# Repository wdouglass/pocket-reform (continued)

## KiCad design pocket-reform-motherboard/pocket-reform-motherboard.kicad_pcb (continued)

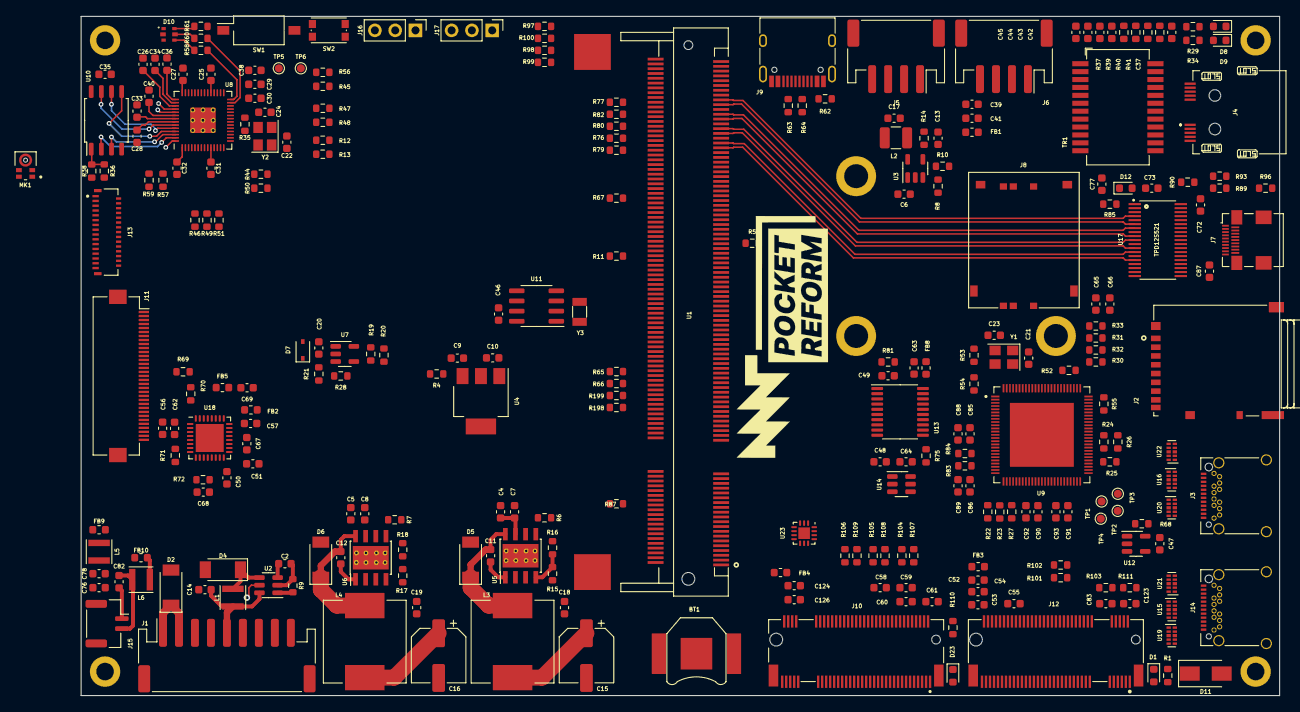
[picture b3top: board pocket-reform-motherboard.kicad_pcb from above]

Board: 6 copper layers, 150.0 x 85.0 mm, 274 parts (0 on the bottom side), 284 nets.

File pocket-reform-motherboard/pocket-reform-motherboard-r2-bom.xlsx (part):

Reference | Value | Footprint | Manufacturer | Manufacturer_No | Qty
C1, C3, C13, C20, C25, C27-C33, C35, C38, C40, C42-C50, C53-C55, C57, C59-C64, 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 | 0.1uF | Capacitor_SMD:C_0402_1005Metric | Samsung | CL05B104KO5NNNC | 66
C2, C4, C5, C39, C51, C56, C65, C98, C105, C107 | 10uF | Capacitor_SMD:C_0603_1608Metric | Samsung | CL10A106MO8NQNC | 10
C6, C17 | 22uF | Capacitor_SMD:C_0603_1608Metric | Samsung | CL10A226MP8NUNE | 2
C7, C8, C11, C12, C18, C19, C52, C58 | 10nF | Capacitor_SMD:C_0603_1608Metric | Samsung | CL10B103KB8NNNC | 8
C9, C10, C26, C34, C36, C41 | 1uF | Capacitor_SMD:C_0603_1608Metric | Samsung | CL10A105KB8NNNC | 6
C14, C83, C123, C124, C126 | 47uF | Capacitor_SMD:C_0603_1608Metric | Murata | GRM188R60J476ME15D | 5
C15, C16 | 330uF | Capacitor_SMD:CP_Elec_6.3x5.4 | Lelon | VZT331M0JTR-0606ACS | 2
C21, C23 | 18pF | Capacitor_SMD:C_0603_1608Metric | Yageo | CC0603JRNPO9BN180 | 2
C22, C24 | 27pF | Capacitor_SMD:C_0603_1608Metric | Yageo | CC0603JRNPO9BN270 | 2
C37 | 1nF | Capacitor_SMD:C_0603_1608Metric | Yageo | CC0603KRX7R9BB102 | 1
C67, C106 | 22uF | Capacitor_SMD:C_0805_2012Metric | Samsung | CL10A226MP8NUNE | 2
C82 | 470nF | Capacitor_SMD:C_0603_1608Metric | Samsung | CL10B474KA8NNNC | 1
C94, C100 | 10uF | Capacitor_SMD:C_0402_1005Metric | Samsung | CL05A106MP5NUNC | 2
C96 | DNP | Capacitor_SMD:C_0402_1005Metric | Samsung | CL05B104KO5NNNC | 1
C102, C103 | 47uF | Capacitor_SMD:C_1206_3216Metric | Murata | GRM31CR61A476ME15L | 2
D1 | LED_MODEM | LED_SMD:LED_0603_1608Metric | Everlight | 19-217/R6C-AL1M2VY/3T | 1
D2, D4-D6 | PMEG4050EP,115 | Diode_SMD:D_SOD-128 | Nexperia | PMEG4050EP,115 | 4
D3 | PMEG1020EA,115 | Diode_SMD:D_SOD-323 | Nexperia | PMEG1020EA,115 | 1
D8, D9 | LED_Small | LED_SMD:LED_0603_1608Metric | Everlight | 19-217/R6C-AL1M2VY/3T | 2
D10 | 19-337/R6GHBHC-A01/2T | footprints:LED_19-337_R6GHBHC-A01_2T | Everlight | 19-337/R6GHBHC-A01/2T | 1
D11 | SS54 | Diode_SMD:D_SMA | MDD | SS54 | 1
D12 | SD0603S040S0R2 | Diode_SMD:D_0603_1608Metric | AVX | SD0603S040S0R2 | 1
D23 | LED_NVME | LED_SMD:LED_0603_1608Metric | Everlight | 19-217/R6C-AL1M2VY/3T | 1
FB1, FB7, FB11 | 220@100MHz 1.4A | Inductor_SMD:L_0603_1608Metric | Murata | BLM18KG221SN1D | 3
FB2-FB4, FB6, FB8-FB10, FB12-FB16 | 100@100MHz 3A | Inductor_SMD:L_0603_1608Metric | Murata | BLM18PG121SN1D | 12
FB5 | DNP | Inductor_SMD:L_0603_1608Metric | Murata | BLM18PG121SN1D | 1
H5, H7 | NGFF-Mount1 | footprints:WA-SMSI-M2 | Wurth | SMTSO2020CTJ | 2
H8, H9 | MountingHole_Pad | footprints:WA-SMSI-M2 | Sinhoo | SMTSO2020CTJ | 2
J1 | CHARGER | Connector_JST:JST_PH_S9B-PH-SM4-TB_1x09-1MP_P2.00mm_Horizontal | HR(Joint Tech Elec) | A2001WR-S-09PD01 | 1
J2 | DM3AT-SF-PEJM5 | footprints:DM3AT-SF-PEJM5 | Hirose | DM3AT-SF-PEJM5 | 1
J3, J14 | USB_C_Receptacle | footprints:MOLEX_105450-0101 | Molex | 105450-0101 | 2
J4 | 9452812561 | footprints:09452812561 | HARTING | 9452812561 | 1
J5 | SYSCTL | Connector_JST:JST_SH_SM04B-SRSS-TB_1x04-1MP_P1.00mm_Horizontal | JST | SM04B-SRSS-TB(LF)(SN) | 1
J6 | USB_INT1 | Connector_JST:JST_SH_SM04B-SRSS-TB_1x04-1MP_P1.00mm_Horizontal | JST | SM04B-SRSS-TB(LF)(SN) | 1
J7 | HDMI_D_1.4 | Connector_HDMI:HDMI_Micro-D_Molex_46765-0x01 | Molex | 467650001 | 1
J8 | SIM_Card | footprints:MOLEX_78800-0001 | Molex | 788000001 | 1
J9 | USB_C_Receptacle_USB2.0 | Connector_USB:USB_C_Receptacle_HRO_TYPE-C-31-M-12 | Korean Hroparts | TYPE-C-31-M-12 | 1
J10 | 1-2199230-6 | footprints:TE_1-2199230-6 | TE | 1-2199230-6 | 1
J11 | Conn_01x33 | Connector_FFC-FPC:Hirose_FH12-33S-0.5SH_1x33-1MP_P0.50mm_Horizontal | Jushuo | AFC07-S33FCC-00 | 1
J12 | 2199230-5 | footprints:TE_2199230-5 | TE | 1-2199230-5 | 1
J13 | FH35C-31S-0.3HW(50) | footprints:TE_3-2328724-1 | TE | 3-2328724-1 | 1
J15 | CONN_SPK | Connector_Molex:Molex_PicoBlade_53261-0271_1x02-1MP_P1.25mm_Horizontal | Molex | 53261-7002 | 1
J16 | SAMTEC_TSM-106-02-X-SH-A | footprints:SAMTEC_TSM-106-02-X-SH-A | Samtec | TSM-106-01-T-SH | 1
J17 | POWSW | Connector_JST:JST_SH_SM02B-SRSS-TB_1x02-1MP_P1.00mm_Horizontal | JST | SM02B-SRSS-TB(LF)(SN) | 1
J18 | CONN_HEAD | Connector_JST:JST_SH_SM05B-SRSS-TB_1x05-1MP_P1.00mm_Horizontal | JST | SM05B-SRSS-TB(LF)(SN) | 1
J20 | QWIIC | Connector_JST:JST_SH_SM04B-SRSS-TB_1x04-1MP_P1.00mm_Horizontal | JST | SM04B-SRSS-TB(LF)(SN) | 1
J21 | USBSEL | Connector_PinHeader_2.00mm:PinHeader_2x03_P2.00mm_Vertical_SMD | Harwin | M22-5320305 | 1
L1 | 22uH | Inductor_SMD:L_Taiyo-Yuden_NR-30xx | YJYCOIN | YNR3015-150M | 1
L2 | 3.3uH | Inductor_SMD:L_1210_3225Metric | Murata | LQH32PN3R3NN0L | 1
L3, L4 | 15uH | Inductor_SMD:L_Vishay_IHLP-4040 | Vishay | IHLP4040DZER150M11 | 2
L5, L6 | 15uH | Inductor_SMD:L_Taiyo-Yuden_NR-30xx | Taiyo Yuden | NRH3012T150MN | 2
R1, R29, R34-R36, R58, R60, R61, R110 | 1k | Resistor_SMD:R_0402_1005Metric | Yageo | RC0402FR-071KL | 9
R2 | 1M | Resistor_SMD:R_0402_1005Metric | Yageo | AC0402FR-071ML | 1
R3 | 90.9K 1% | Resistor_SMD:R_0402_1005Metric | UNI-ROYAL | 0402WGF9092TCE | 1
R4, R5, R9, R11-R13, R19, R27, R33, R44-R46, R50, R53, R54, R65-R67, R81, R103-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 | 0 | Resistor_SMD:R_0402_1005Metric | Panasonic | ERJ2GE0R00X | 27
R6-R8, R69, R70, R87 | 100k | Resistor_SMD:R_0402_1005Metric | Yageo | RC0402FR-07100KL | 6
R10, R15, R17, R20, R22, R24, R26, R28, R30, R38, R52, R56, R68, R72, R75, R85,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 | 10k | Resistor_SMD:R_0402_1005Metric | Yageo | RC0402FR-0710KL | 17
R14 | 8.25k | Resistor_SMD:R_0402_1005Metric | UNI-ROYAL | 0402WGF8251TCE | 1
R16 | 3.16k | Resistor_SMD:R_0402_1005Metric | Yageo | RC0402FR-073K16L | 1
R18 | 5.76k | Resistor_SMD:R_0402_1005Metric | UNI-ROYAL | 0402WGF5761TCE | 1
R21, R55, R62, R74, R78, R86, R88 | DNP | Resistor_SMD:R_0402_1005Metric | DNP | DNP | 7
R23 | 9.53K 1% | Resistor_SMD:R_0402_1005Metric | FH | RC-02W9531FT | 1
R25, R42, R43, R57, R59, R89, R93, R95, R101 | 4.7k | Resistor_SMD:R_0402_1005Metric | Yageo | RC0402FR-074K7L | 9
R37, R39-R41 | 75 1% | Resistor_SMD:R_0402_1005Metric | Panasonic | ERJ2RKF75R0X | 4
R47, R48 | 27.4 | Resistor_SMD:R_0402_1005Metric | UNI-ROYAL | 0402WGF274JTCE | 2
R64 | 2.2k | Resistor_SMD:R_0402_1005Metric | Yageo | RC0402FR-072K2L | 1
R73, R97-R100 | 47k | Resistor_SMD:R_0402_1005Metric | Yageo | AC0402FR-0747KL | 5
R76, R77, R79, R80, R82 | 33 | Resistor_SMD:R_0402_1005Metric | Yageo | RC0402FR-0733RL | 5
R83, R84 | 22k | Resistor_SMD:R_0402_1005Metric | Yageo | AC0402FR-0722KL | 2
R90 | 27k | Resistor_SMD:R_0402_1005Metric | Panasonic | ERJ2RKF2702X | 1
R198, R199 | 49.9 | Resistor_SMD:R_0402_1005Metric | Yageo | RC0402FR-0749R9L | 2
SW1 | SW_DIP_x01 | Button_Switch_SMD:SW_DIP_SPSTx01_Slide_Omron_A6S-110x_W8.9mm_P2.54mm | Dongguan Guangzhu | DSIC01LSGET | 1
SW2 | RESET | Button_Switch_SMD:SW_Push_1P1T_NO_CK_KMR2 | XKB | TS-1185EC-C-D-B | 1
TP5, TP6 | TestPoint | TestPoint:TestPoint_Pad_D1.0mm | DNP | DNP | 2
TR1 | TG111-MSC13LF | Transformer_SMD:Transformer_Ethernet_HALO_TG111-MSC13 | Heling | MT24-S1T1 | 1
U1 | reform2-som-connector | footprints:TE_1473149-4 | TE | 1473149-1 | 1
U2 | MAX1837EUT33+T | Package_TO_SOT_SMD:SOT-23-6 | Maxim | MAX1837EUT33+T | 1
U3 | LM2830XQMFE/NOPB | Package_TO_SOT_SMD:SOT-23-5 | Texas Instruments | LM2830XQMFE/NOPB | 1
U4 | TLV1117-18 | Package_TO_SOT_SMD:SOT-223 | ON | NCV1117ST18T3G | 1
U5, U6 | TPS5450DDAR | Package_SO:TI_SO-PowerPAD-8_ThermalVias | Texas Instruments | TPS5450DDAR | 2
U7 | 74LVC1G34 | Package_TO_SOT_SMD:SOT-353_SC-70-5 | Texas Instruments or UMW | SN74LVC1G34DCKR | 1
U8 | RP2040 | footprints:RP2040-QFN-56 | Raspberry Pi | RP2040 | 1
U9 | TPS7A0533PDBZ | Package_TO_SOT_SMD:SOT-23 | Texas Instruments | TPS7A0533PDBZ | 1
U10 | W25Q32JVSS | Package_SO:SOIC-8_5.23x5.23mm_P1.27mm | Winbond | W25Q32JVSS | 1
U11 | PCF8523T | Package_SO:SOIC-8_3.9x4.9mm_P1.27mm | NXP | PCF8523T/1,118 | 1
U12 | AP22815A | Package_TO_SOT_SMD:SOT-23-5 | Diodes, Inc. | AP22815AWT-7 | 1
U13, U24 | TXS0108EPW | Package_SO:TSSOP-20_4.4x6.5mm_P0.65mm | Texas Instruments | TXS0108EPW | 2
U14 | SN74AVC1T45 | Package_TO_SOT_SMD:SOT-23-6 | Texas Instruments | SN74AVC1T45DBVR | 1
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
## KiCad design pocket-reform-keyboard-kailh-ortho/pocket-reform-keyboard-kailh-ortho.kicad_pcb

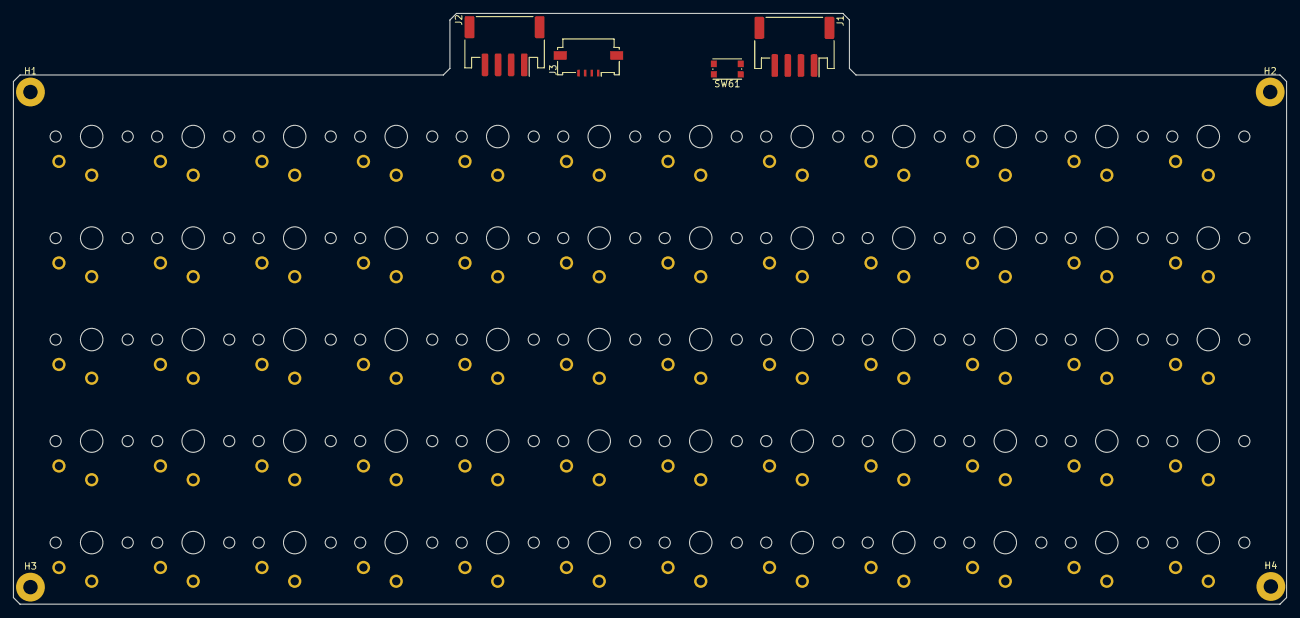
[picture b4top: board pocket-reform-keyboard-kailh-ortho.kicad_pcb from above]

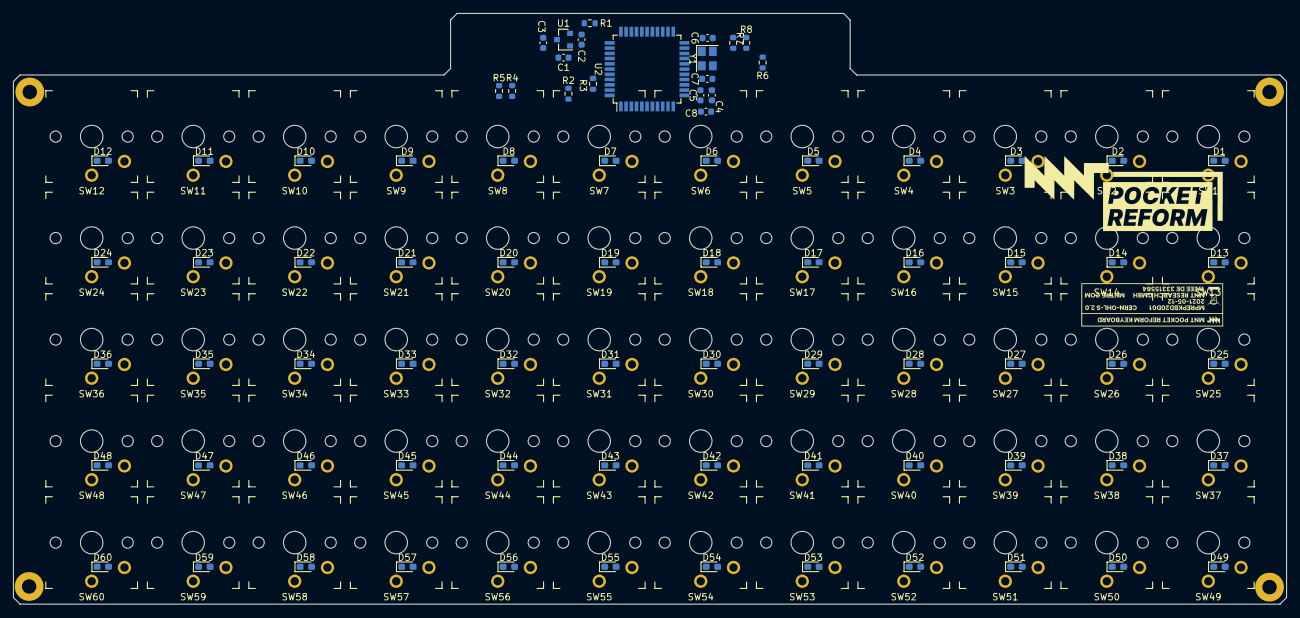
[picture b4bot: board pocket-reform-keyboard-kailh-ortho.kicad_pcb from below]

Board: 2 copper layers, 194.4 x 90.2 mm, 149 parts (81 on the bottom side), 95 nets, no tracks yet.

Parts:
C1, C2, C4, C8: 1uF; C_0603_1608Metric
C3, C5: 0.1uF; C_0603_1608Metric
C6, C7: 18pF; C_0603_1608Metric
D1, D2, D3, D4, D5, D6, D7, D8, D9, D10, D11, D12, D13, D14, D15, D16, D17, D18, D19, D20, D21, D22, D23, D24, D25, D26, D27, D28, D29, D30, D31, D32, D33, D34, D35, D36, D37, D38, D39, D40, D41, D42, D43, D44, D45, D46, D47, D48, D49, D50, D51, D52, D53, D54, D55, D56, D57, D58, D59, D60: MMDL914T1G; D_0603_1608Metric_Pad1.05x0.95mm_HandSolder
GFX1: MNT; pocket-reform
GFX2: MNT; mpre-badge-d1
H1: MH1; MountingHole_2.2mm_M2_Pad
H2: MH2; MountingHole_2.2mm_M2_Pad
H3: MH3; MountingHole_2.2mm_M2_Pad
H4: MH4; MountingHole_2.2mm_M2_Pad
J1: USB; JST_PH_S4B-PH-SM4-TB_1x04-1MP_P2.00mm_Horizontal
J2: UART; JST_PH_S4B-PH-SM4-TB_1x04-1MP_P2.00mm_Horizontal
J3: AUX; Molex_200528-0040_1x04-1MP_P1.00mm_Horizontal
R1, R3, R6: 0; R_0603_1608Metric
R2: 10k; R_0603_1608Metric
R4, R5: 22; R_0603_1608Metric
R7, R8: 4.7k; R_0603_1608Metric
SW1, SW2, SW3, SW4, SW5, SW6, SW7, SW8, SW9, SW10, SW11, SW12, SW13, SW14, SW15, SW16, SW17, SW18, SW19, SW20, SW21, SW22, SW23, SW24, SW25, SW26, SW27, SW28, SW29, SW30, SW31, SW32, SW33, SW34, SW35, SW36, SW37, SW38, SW39, SW40, SW41, SW42, SW43, SW44, SW45, SW46, SW47, SW48, SW49, SW50, SW51, SW52, SW53, SW54, SW55, SW56, SW57, SW58, SW59, SW60: Choc; PG1350
SW61: RESET; SW_Push_1P1T_NO_CK_KMR2
U1: MCP1700-3302E_SOT23; SOT-23
U2: ATMEGA32U4-AU; TQFP-44_10x10mm_P0.8mm
Y1: 16MHz; Crystal_SMD_3225-4Pin_3.2x2.5mm

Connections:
+3V3: C2.1, C4.1, C5.1, J3.1, R2.1, R3.2, R6.2, R7.1, R8.1, U1.2, U2.14, U2.24, U2.34, U2.44
+5V: C1.1, C3.1, J1.1, U1.3, U2.2, U2.7
/Pocket Reform KBD MCU/UD+: R4.1, U2.4
/Pocket Reform KBD MCU/UD-: R5.1, U2.3
COL1: SW1.1, SW13.1, SW25.1, SW37.1, SW49.1, U2.22
COL2: SW2.1, SW14.1, SW26.1, SW38.1, SW50.1, U2.36
COL3: SW3.1, SW15.1, SW27.1, SW39.1, SW51.1, U2.1
COL4: SW4.1, SW16.1, SW28.1, SW40.1, SW52.1, U2.32
COL5: SW5.1, SW17.1, SW29.1, SW41.1, SW53.1, U2.31
COL6: SW6.1, SW18.1, SW30.1, SW42.1, SW54.1, U2.25
COL7: SW7.1, SW19.1, SW31.1, SW43.1, SW55.1, U2.37
COL8: SW8.1, SW20.1, SW32.1, SW44.1, SW56.1, U2.38
COL9: SW9.1, SW21.1, SW33.1, SW45.1, SW57.1, U2.39
COL10: SW10.1, SW22.1, SW34.1, SW46.1, SW58.1, U2.40
COL11: SW11.1, SW23.1, SW35.1, SW47.1, SW59.1, U2.41
COL12: SW12.1, SW24.1, SW36.1, SW48.1, SW60.1, U2.12
D+: J1.3, R4.2
D-: J1.2, R5.2
DISP_SCL: J3.2, R8.2, U2.18
DISP_SDA: J3.3, R7.2, U2.19
GND: C1.2, C2.2, C3.2, C4.2, C5.2, C6.2, C7.2, C8.2, H1.1, H2.1, H3.1, H4.1, J1.4, J2.4, J3.4, R1.1, SW61.2, U1.1, U2.5, U2.15, U2.23, U2.35, U2.43, Y1.2, Y1.4
unnamed: C6.1, U2.17, Y1.1
unnamed: C7.1, U2.16, Y1.3
unnamed: C8.1, U2.6
unnamed: D1.2, SW1.2
unnamed: D2.2, SW2.2
unnamed: D3.2, SW3.2
unnamed: D4.2, SW4.2
unnamed: D5.2, SW5.2
unnamed: D6.2, SW6.2
unnamed: D7.2, SW7.2
unnamed: D8.2, SW8.2
unnamed: D9.2, SW9.2
unnamed: D10.2, SW10.2
unnamed: D11.2, SW11.2
unnamed: D12.2, SW12.2
unnamed: D13.2, SW13.2
unnamed: D14.2, SW14.2
unnamed: D15.2, SW15.2
unnamed: D16.2, SW16.2
unnamed: D17.2, SW17.2
unnamed: D18.2, SW18.2
unnamed: D19.2, SW19.2
unnamed: D20.2, SW20.2
unnamed: D21.2, SW21.2
unnamed: D22.2, SW22.2
unnamed: D23.2, SW23.2
unnamed: D24.2, SW24.2
unnamed: D25.2, SW25.2
unnamed: D26.2, SW26.2
unnamed: D27.2, SW27.2
unnamed: D28.2, SW28.2
unnamed: D29.2, SW29.2
unnamed: D30.2, SW30.2
unnamed: D31.2, SW31.2
unnamed: D32.2, SW32.2
unnamed: D33.2, SW33.2
unnamed: D34.2, SW34.2
unnamed: D35.2, SW35.2
unnamed: D36.2, SW36.2
unnamed: D37.2, SW37.2
unnamed: D38.2, SW38.2
unnamed: D39.2, SW39.2
unnamed: D40.2, SW40.2
unnamed: D41.2, SW41.2
unnamed: D42.2, SW42.2
unnamed: D43.2, SW43.2
unnamed: D44.2, SW44.2
unnamed: D45.2, SW45.2
unnamed: D46.2, SW46.2
unnamed: D47.2, SW47.2
unnamed: D48.2, SW48.2
unnamed: D49.2, SW49.2
unnamed: D50.2, SW50.2
unnamed: D51.2, SW51.2
unnamed: D52.2, SW52.2
unnamed: D53.2, SW53.2
unnamed: D54.2, SW54.2
unnamed: D55.2, SW55.2
unnamed: D56.2, SW56.2
unnamed: D57.2, SW57.2
unnamed: D58.2, SW58.2
unnamed: D59.2, SW59.2
unnamed: D60.2, SW60.2
unnamed: J2.1, R6.1
unnamed: R3.1, U2.42
PROG: R1.2, U2.33
RESET: R2.2, SW61.1, U2.13
ROW1: D1.1, D2.1, D3.1, D4.1, D5.1, D6.1, D7.1, D8.1, D9.1, D10.1, D11.1, D12.1, U2.30
ROW2: D13.1, D14.1, D15.1, D16.1, D17.1, D18.1, D19.1, D20.1, D21.1, D22.1, D23.1, D24.1, U2.29
ROW3: D25.1, D26.1, D27.1, D28.1, D29.1, D30.1, D31.1, D32.1, D33.1, D34.1, D35.1, D36.1, U2.28
ROW4: D37.1, D38.1, D39.1, D40.1, D41.1, D42.1, D43.1, D44.1, D45.1, D46.1, D47.1, D48.1, U2.27
ROW5: D49.1, D50.1, D51.1, D52.1, D53.1, D54.1, D55.1, D56.1, D57.1, D58.1, D59.1, D60.1, U2.26
UART_RX: J2.2, U2.20
UART_TX: J2.3, U2.21

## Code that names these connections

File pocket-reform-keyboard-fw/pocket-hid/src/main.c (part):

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#define PIN_SDA 0
#define PIN_SCL 1

#define PIN_UART_TX 4
#define PIN_UART_RX 5

#define PIN_ROW1 19
#define PIN_ROW2 20
#define PIN_ROW3 23
#define PIN_ROW4 22
#define PIN_ROW5 21
#define PIN_ROW6 18

#define PIN_COL1 6
#define PIN_COL2 7
#define PIN_COL3 8
#define PIN_COL4 9
#define PIN_COL5 10
#define PIN_COL6 11
#define PIN_COL7 12
#define PIN_COL8 13
#define PIN_COL9 14
#define PIN_COL10 15
#define PIN_COL11 16
#define PIN_COL12 17

#define PIN_LEDS 24

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  uart_set_format(UART_ID, DATA_BITS, STOP_BITS, PARITY);
  uart_set_hw_flow(UART_ID, false, false);
  uart_set_fifo_enabled(UART_ID, true);
  gpio_set_function(PIN_UART_TX, GPIO_FUNC_UART);
  gpio_set_function(PIN_UART_RX, GPIO_FUNC_UART);
  unsigned int UART_IRQ = UART_ID == uart0 ? UART0_IRQ : UART1_IRQ;

  gpio_init(PIN_LEDS);
  gpio_set_dir(PIN_LEDS, true); // output

  gpio_init(PIN_COL1);
  gpio_set_dir(PIN_COL1, true);
  gpio_init(PIN_COL2);
  gpio_set_dir(PIN_COL2, true);
  gpio_init(PIN_COL3);
  gpio_set_dir(PIN_COL3, true);
  gpio_init(PIN_COL4);
  gpio_set_dir(PIN_COL4, true);
  gpio_init(PIN_COL5);
  gpio_set_dir(PIN_COL5, true);
  gpio_init(PIN_COL6);
  gpio_set_dir(PIN_COL6, true);
  gpio_init(PIN_COL7);
  gpio_set_dir(PIN_COL7, true);
  gpio_init(PIN_COL8);
  gpio_set_dir(PIN_COL8, true);
  gpio_init(PIN_COL9);
  gpio_set_dir(PIN_COL9, true);
  gpio_init(PIN_COL10);
  gpio_set_dir(PIN_COL10, true);
  gpio_init(PIN_COL11);
  gpio_set_dir(PIN_COL11, true);
  gpio_init(PIN_COL12);
  gpio_set_dir(PIN_COL12, true);

  gpio_init(PIN_ROW1);
  gpio_set_dir(PIN_ROW1, false);
  gpio_pull_down(PIN_ROW1);
  gpio_init(PIN_ROW2);
  gpio_set_dir(PIN_ROW2, false);
  gpio_pull_down(PIN_ROW2);
  gpio_init(PIN_ROW3);
  gpio_set_dir(PIN_ROW3, false);
  gpio_pull_down(PIN_ROW3);
  gpio_init(PIN_ROW4);
  gpio_set_dir(PIN_ROW4, false);
  gpio_pull_down(PIN_ROW4);
  gpio_init(PIN_ROW5);
  gpio_set_dir(PIN_ROW5, false);
  gpio_pull_down(PIN_ROW5);
  gpio_init(PIN_ROW6);
  gpio_set_dir(PIN_ROW6, false);
  gpio_pull_down(PIN_ROW6);
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  }

  for (int x = 0; x < KBD_COLS; x++) {
    gpio_put(PIN_COL1, 0);
    gpio_put(PIN_COL2, 0);
    gpio_put(PIN_COL3, 0);
    gpio_put(PIN_COL4, 0);
    gpio_put(PIN_COL5, 0);
    gpio_put(PIN_COL6, 0);
    gpio_put(PIN_COL7, 0);
    gpio_put(PIN_COL8, 0);
    gpio_put(PIN_COL9, 0);
    gpio_put(PIN_COL10, 0);
    gpio_put(PIN_COL11, 0);
    gpio_put(PIN_COL12, 0);

    switch (x) {
    case 0: gpio_put(PIN_COL1, 1); break;
    case 1: gpio_put(PIN_COL2, 1); break;
    case 2: gpio_put(PIN_COL3, 1); break;
    case 3: gpio_put(PIN_COL4, 1); break;
    case 4: gpio_put(PIN_COL5, 1); break;
    case 5: gpio_put(PIN_COL6, 1); break;
    case 6: gpio_put(PIN_COL7, 1); break;
    case 7: gpio_put(PIN_COL8, 1); break;
    case 8: gpio_put(PIN_COL9, 1); break;
    case 9: gpio_put(PIN_COL10, 1); break;
    case 10: gpio_put(PIN_COL11, 1); break;
    case 11: gpio_put(PIN_COL12, 1); break;
    }

    // wait for signal to stabilize
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      uint8_t  debounced_pressed = 0;

      switch (y) {
      case 0:  pressed = gpio_get(PIN_ROW1); break;
      case 1:  pressed = gpio_get(PIN_ROW2); break;
      case 2:  pressed = gpio_get(PIN_ROW3); break;
      case 3:  pressed = gpio_get(PIN_ROW4); break;
      case 4:  pressed = gpio_get(PIN_ROW5); break;
      case 5:  pressed = gpio_get(PIN_ROW6); break;
      }

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
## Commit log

2021-04-30 initial keyboard pcb WIP
2021-05-11 keyboard: first routed draft
2021-05-17 keyboard: D-1, sent to fab
2021-05-17 add README
2021-07-28 add 13x8cm motherboard mockup
2021-11-19 WIP: component sketch of kailh ortho kbd 7 inch test
2022-05-31 motherboard D-1 first schematic and placement
2022-06-08 motherboard: first routing
2022-06-13 motherboard: routing snapshot
2022-06-14 snapshot before replacing usb7002
2022-06-14 routing snapshot with TUSB8040
2022-06-17 motherboard: resolve LCSC parts
2022-06-28 keyboard: tweak trackball mount, wire up tb buttons and leds
2022-06-28 motherboard: d-1 ordered version
2022-08-25 WIP: keyboard/trackball firmware initial
2022-08-25 move old keyboard to attic
2022-08-25 keyboard: add D-1 version (beware, has hw bugs)
2022-08-25 WIP: pocket sysctl firmware initial
2022-08-25 motherboard: add some notes
2022-08-25 WIP gauge reporting experiment
2022-08-26 WIP HID: port oled/font code
2022-08-26 HID: fiddle with types to make compiler happy
2022-08-26 HID: fix more c typing problems
2022-08-26 HID: fix display width
2022-12-15 keyboard d-2 done and exported for assembly
2022-12-26 kbd: oled fixes and backlight WIP
2023-01-12 pocket HID: let PIOs handle the LED backlight; introduce hue/value setting via trackball;
2023-01-12 pocket HID: tweak keyboard matrix
2023-02-21 pocket-hid: add backlight control commands etc
2023-03-20 pocket-hid: fix compiler warnings; lower oled brightness
2023-04-12 charger snapshot
2023-04-12 add WIP panel and bezel PCBs
2023-04-12 add missing keyboard back PCB
2023-08-07 d-2 pcbs TODO
2023-08-07 sysctl: spi pins loading test
2023-08-14 keyboard: formatting
2023-08-14 sysctl: increase charge current, put 100ms sleep in timeout state
2023-08-14 sysctl: flash: add -f
2023-08-24 WIP: work on mb schematic
2023-08-24 WIP: motherboard: move things around
2023-08-25 WIP: mb: pushing things around
2023-08-25 WIP: mb: more shuffling
2023-08-25 WIP: mb: add lib item
2023-09-28 motherboard schematics basically done
2023-09-29 D-2 fully routed
2023-10-03 motherboard: D-3 production snapshot
2023-10-03 keyboard D-3: production snapshot
2023-11-08 keyboard-fw: update for latest tinyusb; enable usb Errata RP2040-E5
2023-11-20 mb: snapshot before TUSB8041 change
2023-11-22 WIP mb audio rerouting
2023-11-24 motherboard: R-1
2023-12-06 snapshot before change to MP2650
2023-12-12 sysctl: updates for motherboard r-1 - add usb power sourcing enable - add latch chip support for power/display enables - update modem pins - lower system freq to 48mhz
2023-12-12 sysctl: add pico_extras support for rtc/sleep; add usb enum and xosc startup fixes
2023-12-27 add cable specs
2023-12-27 add latest case files
2023-12-27 add case plate parts
2023-12-27 sysctl: debug charger WIP
2023-12-27 add trackball cup model
2023-12-27 update charger pcb
2023-12-27 update motherboard pcb
2023-12-27 update keyboard fw
2023-12-27 add headphone/switch pcb
2023-12-27 update keyboard pcb
2024-01-16 kbd: change power key to hyper+return, test wake with f12
2024-01-17 sysctl: add som wake command
2024-01-19 add tweaked battery holder models
2024-02-23 add display pdf
2024-04-08 WIP: init real SPI
2024-04-12 sysctl: implement more spi and serial reporting functionality
2024-04-12 pocket-hid: port OLED menu from reform incl battery status, some refactoring
2024-04-17 cleanup for release
2024-04-17 add production keyboard lettering
2024-04-17 keyboard fw polishing for release
2024-04-17 various kicad bumps
2024-04-17 sysctl: remove 2 todos
2024-05-03 sysctl: add ACM_ENABLED and FACTORY_MODE defines
2024-05-06 hid: remove non-functional usb power state and poll real power state
2024-05-06 sysctl: fix logic error/hang around spi poweroff
2024-05-09 implement console based keyboard tester
2024-05-30 add a3 pdf schematics poster
2024-05-31 add script to install all fw build dependencies
2024-05-31 also install tio
2024-05-31 keyboard-fw: make it so that the trackball buttons do what's said in the manual
2024-06-03 hid: finalize trackball button layout
2024-06-03 hid: make flash.sh slightly less dangerous
2024-06-04 fix cmake tinyusb location
2024-06-04 set factory mode in the system controller
2024-06-04 fix keymap to be closer to planck
2024-06-04 swap middle and scroll trackball buttons
2024-06-04 rest in the keyboard main loop, to save battery
